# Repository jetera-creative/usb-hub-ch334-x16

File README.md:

# USB 2.0 HighSpeed x16 hub with CH334

Low cost solution about USB hub with 16 ports.
The circuit design integrates 5 chips of CH334.

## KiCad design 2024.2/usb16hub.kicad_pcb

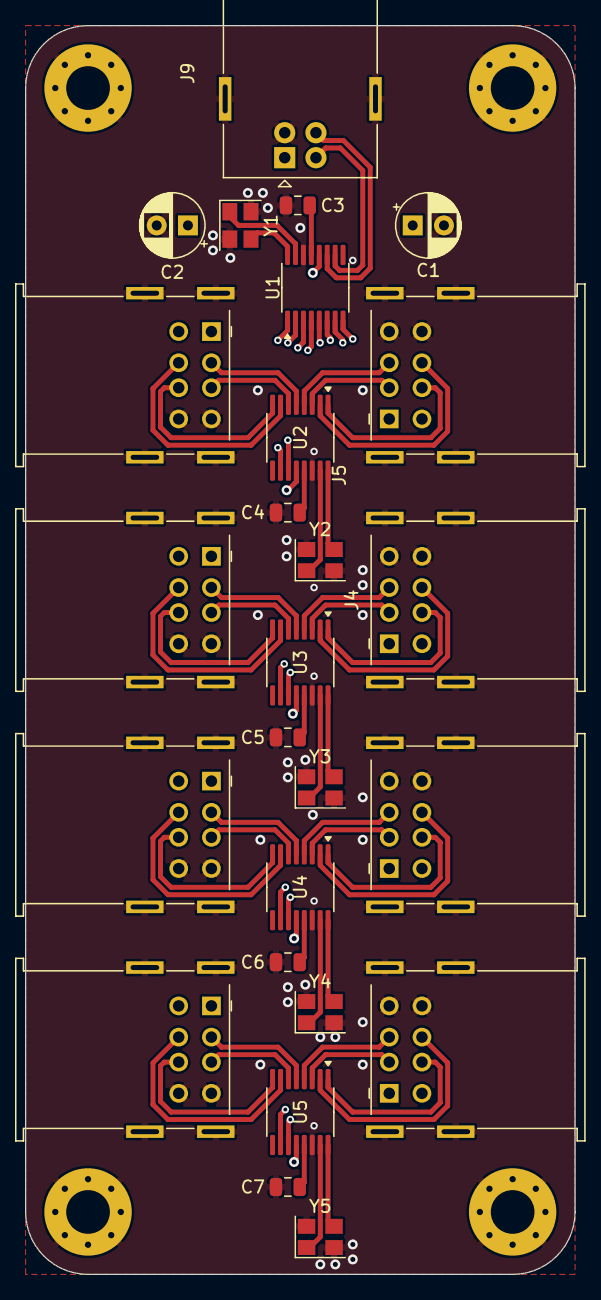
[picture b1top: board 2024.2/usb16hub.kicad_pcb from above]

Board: 4 copper layers, 44.0 x 100.0 mm, 30 parts (0 on the bottom side), 59 nets.

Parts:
C1, C2: 270uF; CP_Radial_D5.0mm_P2.50mm
C3, C4, C5, C6, C7: 4.7uF; C_0805_2012Metric
H1, H2, H3, H4: MountingHole_Pad; MountingHole_3.5mm_Pad_Via
J1, J2, J3, J4, J5, J6, J7, J8: USB_A_Stacked; USB_A_Wuerth_61400826021_Horizontal_Stacked
J9: USB_B; USB_B_OST_USB-B1HSxx_Horizontal
U1, U2, U3, U4, U5: CH334R; QSOP-16_3.9x4.9mm_P0.635mm
Y1, Y2, Y3, Y4, Y5: Crystal_GND24_Small; Crystal_SMD_3225-4Pin_3.2x2.5mm

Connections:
+5V: C1.1, C2.1, J1.1 (VBUS1), J1.5 (VBUS2), J2.1 (VBUS1), J2.5 (VBUS2), J3.1 (VBUS1), J3.5 (VBUS2), J4.1 (VBUS1), J4.5 (VBUS2), J5.1 (VBUS1), J5.5 (VBUS2), J6.1 (VBUS1), J6.5 (VBUS2), J7.1 (VBUS1), J7.5 (VBUS2), J8.1 (VBUS1), J8.5 (VBUS2), J9.1 (VBUS), U1.12 (5V), U2.12 (5V), U3.12 (5V), U4.12 (5V), U5.12 (5V)
GND: C1.2, C2.2, C3.2, C4.2, C5.2, C6.2, C7.2, H1.1, H2.1, H3.1, H4.1, J1.4 (GND1), J1.8 (GND2), J1.9 (Shield), J2.4 (GND1), J2.8 (GND2), J2.9 (Shield), J3.4 (GND1), J3.8 (GND2), J3.9 (Shield), J4.4 (GND1), J4.8 (GND2), J4.9 (Shield), J5.4 (GND1), J5.8 (GND2), J5.9 (Shield), J6.4 (GND1), J6.8 (GND2), J6.9 (Shield), J7.4 (GND1), J7.8 (GND2), J7.9 (Shield), J8.4 (GND1), J8.8 (GND2), J8.9 (Shield), J9.4 (GND), J9.5 (Shield), U1.14 (GND), U2.14 (GND), U3.14 (GND), U4.14 (GND), U5.14 (GND), Y1.2, Y1.4, Y2.2, Y2.4, Y3.2, Y3.4, Y4.2, Y4.4, Y5.2, Y5.4
unnamed: J1.3 (D1+), U2.6 (D2+)
unnamed: J1.2 (D1-), U2.5 (D2-)
unnamed: J1.7 (D2+), U2.8 (D1+)
unnamed: J1.6 (D2-), U2.7 (D1-)
unnamed: J2.3 (D1+), U2.4 (D3+)
unnamed: J2.2 (D1-), U2.3 (D3-)
unnamed: J2.7 (D2+), U2.2 (D4+)
unnamed: J2.6 (D2-), U2.1 (D4-)
unnamed: J3.3 (D1+), U3.6 (D2+)
unnamed: J3.2 (D1-), U3.5 (D2-)
unnamed: J3.7 (D2+), U3.8 (D1+)
unnamed: J3.6 (D2-), U3.7 (D1-)
unnamed: J4.3 (D1+), U3.4 (D3+)
unnamed: J4.2 (D1-), U3.3 (D3-)
unnamed: J4.7 (D2+), U3.2 (D4+)
unnamed: J4.6 (D2-), U3.1 (D4-)
unnamed: J5.3 (D1+), U4.6 (D2+)
unnamed: J5.2 (D1-), U4.5 (D2-)
unnamed: J5.7 (D2+), U4.8 (D1+)
unnamed: J5.6 (D2-), U4.7 (D1-)
unnamed: J6.3 (D1+), U4.4 (D3+)
unnamed: J6.2 (D1-), U4.3 (D3-)
unnamed: J6.7 (D2+), U4.2 (D4+)
unnamed: J6.6 (D2-), U4.1 (D4-)
unnamed: J7.3 (D1+), U5.6 (D2+)
unnamed: J7.2 (D1-), U5.5 (D2-)
unnamed: J7.7 (D2+), U5.8 (D1+)
unnamed: J7.6 (D2-), U5.7 (D1-)
unnamed: J8.3 (D1+), U5.4 (D3+)
unnamed: J8.2 (D1-), U5.3 (D3-)
unnamed: J8.7 (D2+), U5.2 (D4+)
unnamed: J8.6 (D2-), U5.1 (D4-)
unnamed: J9.3 (D+), U1.11 (DU+)
unnamed: J9.2 (D-), U1.10 (DU-)
unnamed: C3.1, U1.13 (3V3)
unnamed: U1.8 (D1+), U5.11 (DU+)
unnamed: U1.7 (D1-), U5.10 (DU-)
unnamed: U1.6 (D2+), U4.11 (DU+)
unnamed: U1.5 (D2-), U4.10 (DU-)
unnamed: U1.4 (D3+), U3.11 (DU+)
unnamed: U1.3 (D3-), U3.10 (DU-)
unnamed: U1.2 (D4+), U2.11 (DU+)
unnamed: U1.1 (D4-), U2.10 (DU-)
unnamed: U1.16 (XI), Y1.3
unnamed: U1.15 (XO), Y1.1
unnamed: C4.1, U2.13 (3V3)
unnamed: U2.16 (XI), Y2.3
unnamed: U2.15 (XO), Y2.1
unnamed: C5.1, U3.13 (3V3)
unnamed: U3.16 (XI), Y3.3
unnamed: U3.15 (XO), Y3.1
unnamed: C6.1, U4.13 (3V3)
unnamed: U4.16 (XI), Y4.3
unnamed: U4.15 (XO), Y4.1
unnamed: C7.1, U5.13 (3V3)
unnamed: U5.16 (XI), Y5.3
unnamed: U5.15 (XO), Y5.1

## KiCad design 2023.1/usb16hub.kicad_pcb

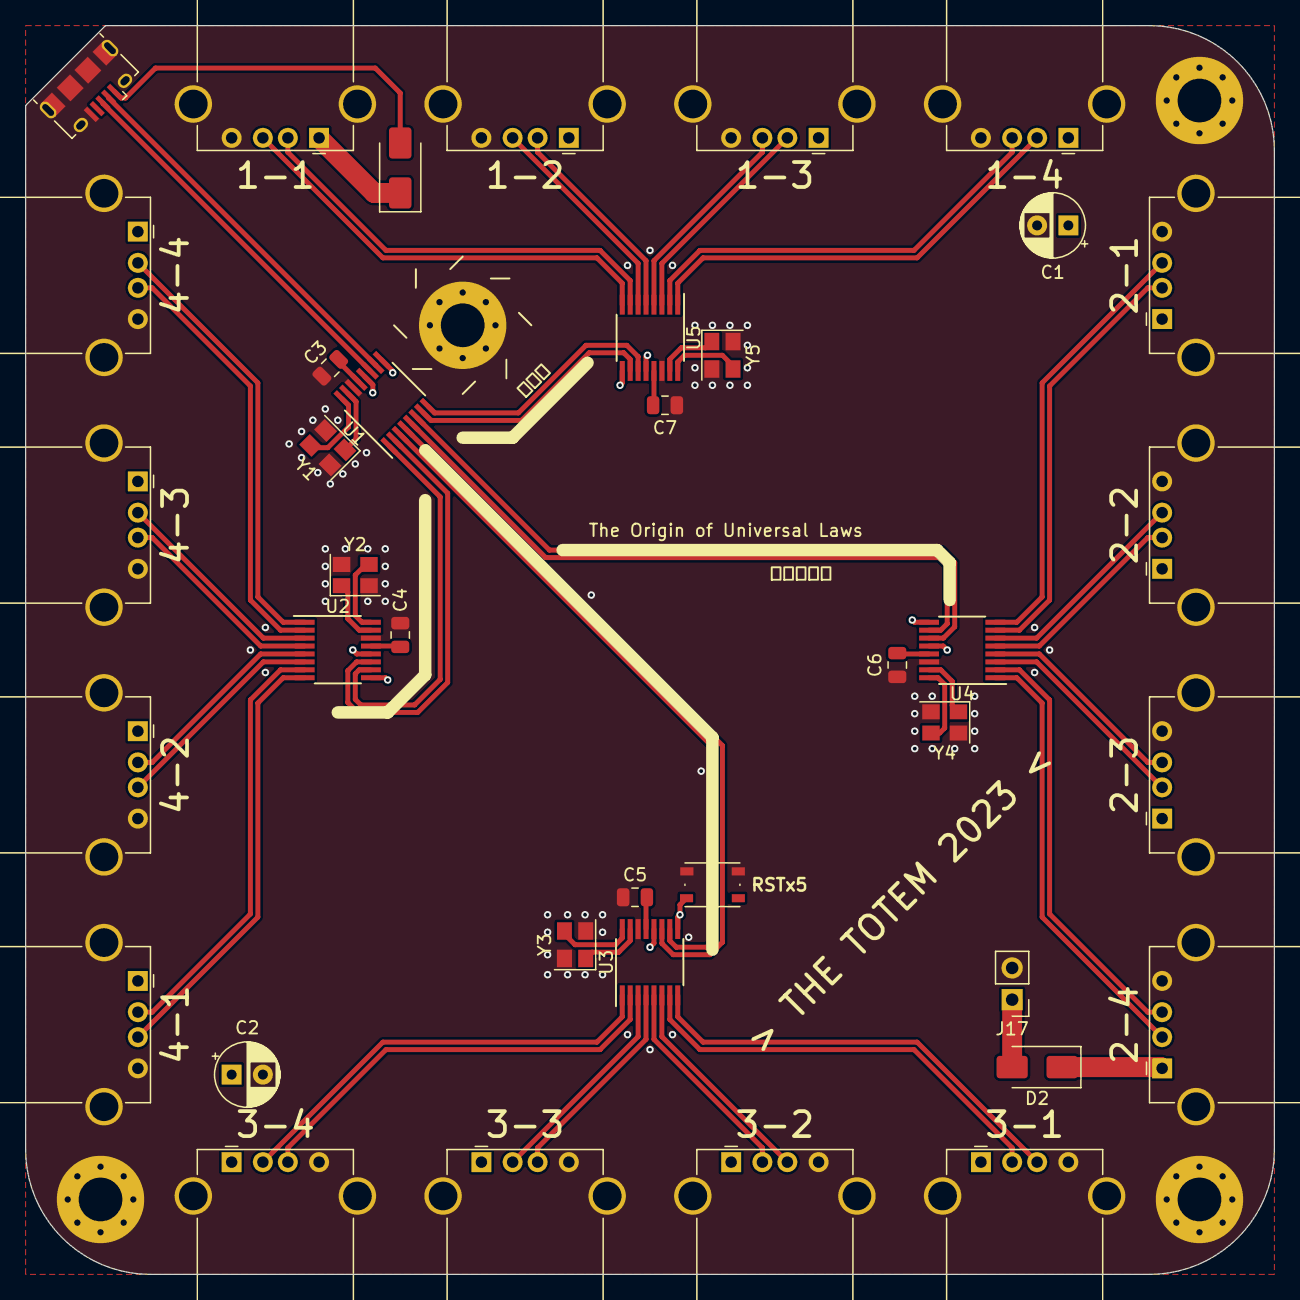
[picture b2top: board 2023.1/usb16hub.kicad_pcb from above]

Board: 4 copper layers, 100.0 x 100.0 mm, 42 parts (0 on the bottom side), 62 nets.

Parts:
C1, C2: 270uF; CP_Radial_D5.0mm_P2.50mm
C3, C4, C5, C6, C7: 4.7uF; C_0805_2012Metric
D1, D2: D_Schottky; D_SMA
H1, H2, H3, H4: MountingHole_Pad; MountingHole_3.5mm_Pad_Via
J1, J2, J3, J4, J5, J6, J7, J8, J9, J10, J11, J12, J13, J14, J15, J16: USB_A; USB_A_Stewart_SS-52100-001_Horizontal
J17: Conn_01x02; PinHeader_1x02_P2.54mm_Vertical
J18: USB_B_Micro; USB_Micro-B_Amphenol_10118194_Horizontal
SW1: SW_Push; SW_Push_1P1T_NO_Vertical_Wuerth_434133025816
U1, U2, U3, U4, U5: CH334R; QSOP-16_3.9x4.9mm_P0.635mm
Y1, Y2, Y3, Y4, Y5: Crystal_GND24_Small; Crystal_SMD_3225-4Pin_3.2x2.5mm

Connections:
+5V: C1.1, C2.1, D1.1 (K), D2.1 (K), J1.1 (VBUS), J2.1 (VBUS), J3.1 (VBUS), J4.1 (VBUS), J5.1 (VBUS), J6.1 (VBUS), J7.1 (VBUS), J8.1 (VBUS), J9.1 (VBUS), J10.1 (VBUS), J11.1 (VBUS), J12.1 (VBUS), J13.1 (VBUS), J14.1 (VBUS), J15.1 (VBUS), J16.1 (VBUS), U1.12 (5V), U2.12 (5V), U3.12 (5V), U4.12 (5V), U5.12 (5V)
GND: C1.2, C2.2, C3.2, C4.2, C5.2, C6.2, C7.2, H1.1, H2.1, H3.1, H4.1, J1.4 (GND), J1.5 (Shield), J2.4 (GND), J2.5 (Shield), J3.4 (GND), J3.5 (Shield), J4.4 (GND), J4.5 (Shield), J5.4 (GND), J5.5 (Shield), J6.4 (GND), J6.5 (Shield), J7.4 (GND), J7.5 (Shield), J8.4 (GND), J8.5 (Shield), J9.4 (GND), J9.5 (Shield), J10.4 (GND), J10.5 (Shield), J11.4 (GND), J11.5 (Shield), J12.4 (GND), J12.5 (Shield), J13.4 (GND), J13.5 (Shield), J14.4 (GND), J14.5 (Shield), J15.4 (GND), J15.5 (Shield), J16.4 (GND), J16.5 (Shield), J17.2, J18.5 (GND), J18.6 (Shield), SW1.2, U1.14 (GND), U2.14 (GND), U3.14 (GND), U4.14 (GND), U5.14 (GND), Y1.2, Y1.4, Y2.2, Y2.4, Y3.2, Y3.4, Y4.2, Y4.4, Y5.2, Y5.4
unnamed: D1.2 (A), J18.1 (VBUS)
unnamed: D2.2 (A), J17.1
unnamed: J1.3 (D+), U2.8 (D1+)
unnamed: J1.2 (D-), U2.7 (D1-)
unnamed: J2.3 (D+), U2.6 (D2+)
unnamed: J2.2 (D-), U2.5 (D2-)
unnamed: J3.3 (D+), U2.4 (D3+)
unnamed: J3.2 (D-), U2.3 (D3-)
unnamed: J4.3 (D+), U2.2 (D4+)
unnamed: J4.2 (D-), U2.1 (D4-)
unnamed: J5.3 (D+), U3.8 (D1+)
unnamed: J5.2 (D-), U3.7 (D1-)
unnamed: J6.3 (D+), U3.6 (D2+)
unnamed: J6.2 (D-), U3.5 (D2-)
unnamed: J7.3 (D+), U3.4 (D3+)
unnamed: J7.2 (D-), U3.3 (D3-)
unnamed: J8.3 (D+), U3.2 (D4+)
unnamed: J8.2 (D-), U3.1 (D4-)
unnamed: J9.3 (D+), U4.8 (D1+)
unnamed: J9.2 (D-), U4.7 (D1-)
unnamed: J10.3 (D+), U4.6 (D2+)
unnamed: J10.2 (D-), U4.5 (D2-)
unnamed: J11.3 (D+), U4.4 (D3+)
unnamed: J11.2 (D-), U4.3 (D3-)
unnamed: J12.3 (D+), U4.2 (D4+)
unnamed: J12.2 (D-), U4.1 (D4-)
unnamed: J13.3 (D+), U5.8 (D1+)
unnamed: J13.2 (D-), U5.7 (D1-)
unnamed: J14.3 (D+), U5.6 (D2+)
unnamed: J14.2 (D-), U5.5 (D2-)
unnamed: J15.3 (D+), U5.4 (D3+)
unnamed: J15.2 (D-), U5.3 (D3-)
unnamed: J16.3 (D+), U5.2 (D4+)
unnamed: J16.2 (D-), U5.1 (D4-)
unnamed: J18.3 (D+), U1.11 (DU+)
unnamed: J18.2 (D-), U1.10 (DU-)
unnamed: C3.1, U1.13 (3V3)
unnamed: U1.8 (D1+), U5.11 (DU+)
unnamed: U1.7 (D1-), U5.10 (DU-)
unnamed: U1.6 (D2+), U4.11 (DU+)
unnamed: U1.5 (D2-), U4.10 (DU-)
unnamed: U1.4 (D3+), U3.11 (DU+)
unnamed: U1.3 (D3-), U3.10 (DU-)
unnamed: U1.2 (D4+), U2.11 (DU+)
unnamed: U1.1 (D4-), U2.10 (DU-)
unnamed: U1.16 (XI), Y1.3
unnamed: U1.15 (XO), Y1.1
unnamed: C4.1, U2.13 (3V3)
unnamed: U2.16 (XI), Y2.3
unnamed: U2.15 (XO), Y2.1
unnamed: C5.1, U3.13 (3V3)
unnamed: U3.16 (XI), Y3.3
unnamed: U3.15 (XO), Y3.1
unnamed: C6.1, U4.13 (3V3)
unnamed: U4.16 (XI), Y4.3
unnamed: U4.15 (XO), Y4.1
unnamed: C7.1, U5.13 (3V3)
unnamed: U5.16 (XI), Y5.3
unnamed: U5.15 (XO), Y5.1
RST: SW1.1, U1.9 (~RST), U2.9 (~RST), U3.9 (~RST), U4.9 (~RST), U5.9 (~RST)

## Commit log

2024-04-14 2023.1
2024-11-04 2024.1
2024-11-09 2024.2

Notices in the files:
2023.1/usb16hub.kicad_pcb:
https://creativecommons.org/licenses/by-sa/4.0/legalcode.en
Use of this PCB design is governed under the CC BY-SA 4.0 International license.
© 2023 JetERA Creative
B.SilkS
2024.2/usb16hub.kicad_pcb:
© 2024 JetERA Creative
